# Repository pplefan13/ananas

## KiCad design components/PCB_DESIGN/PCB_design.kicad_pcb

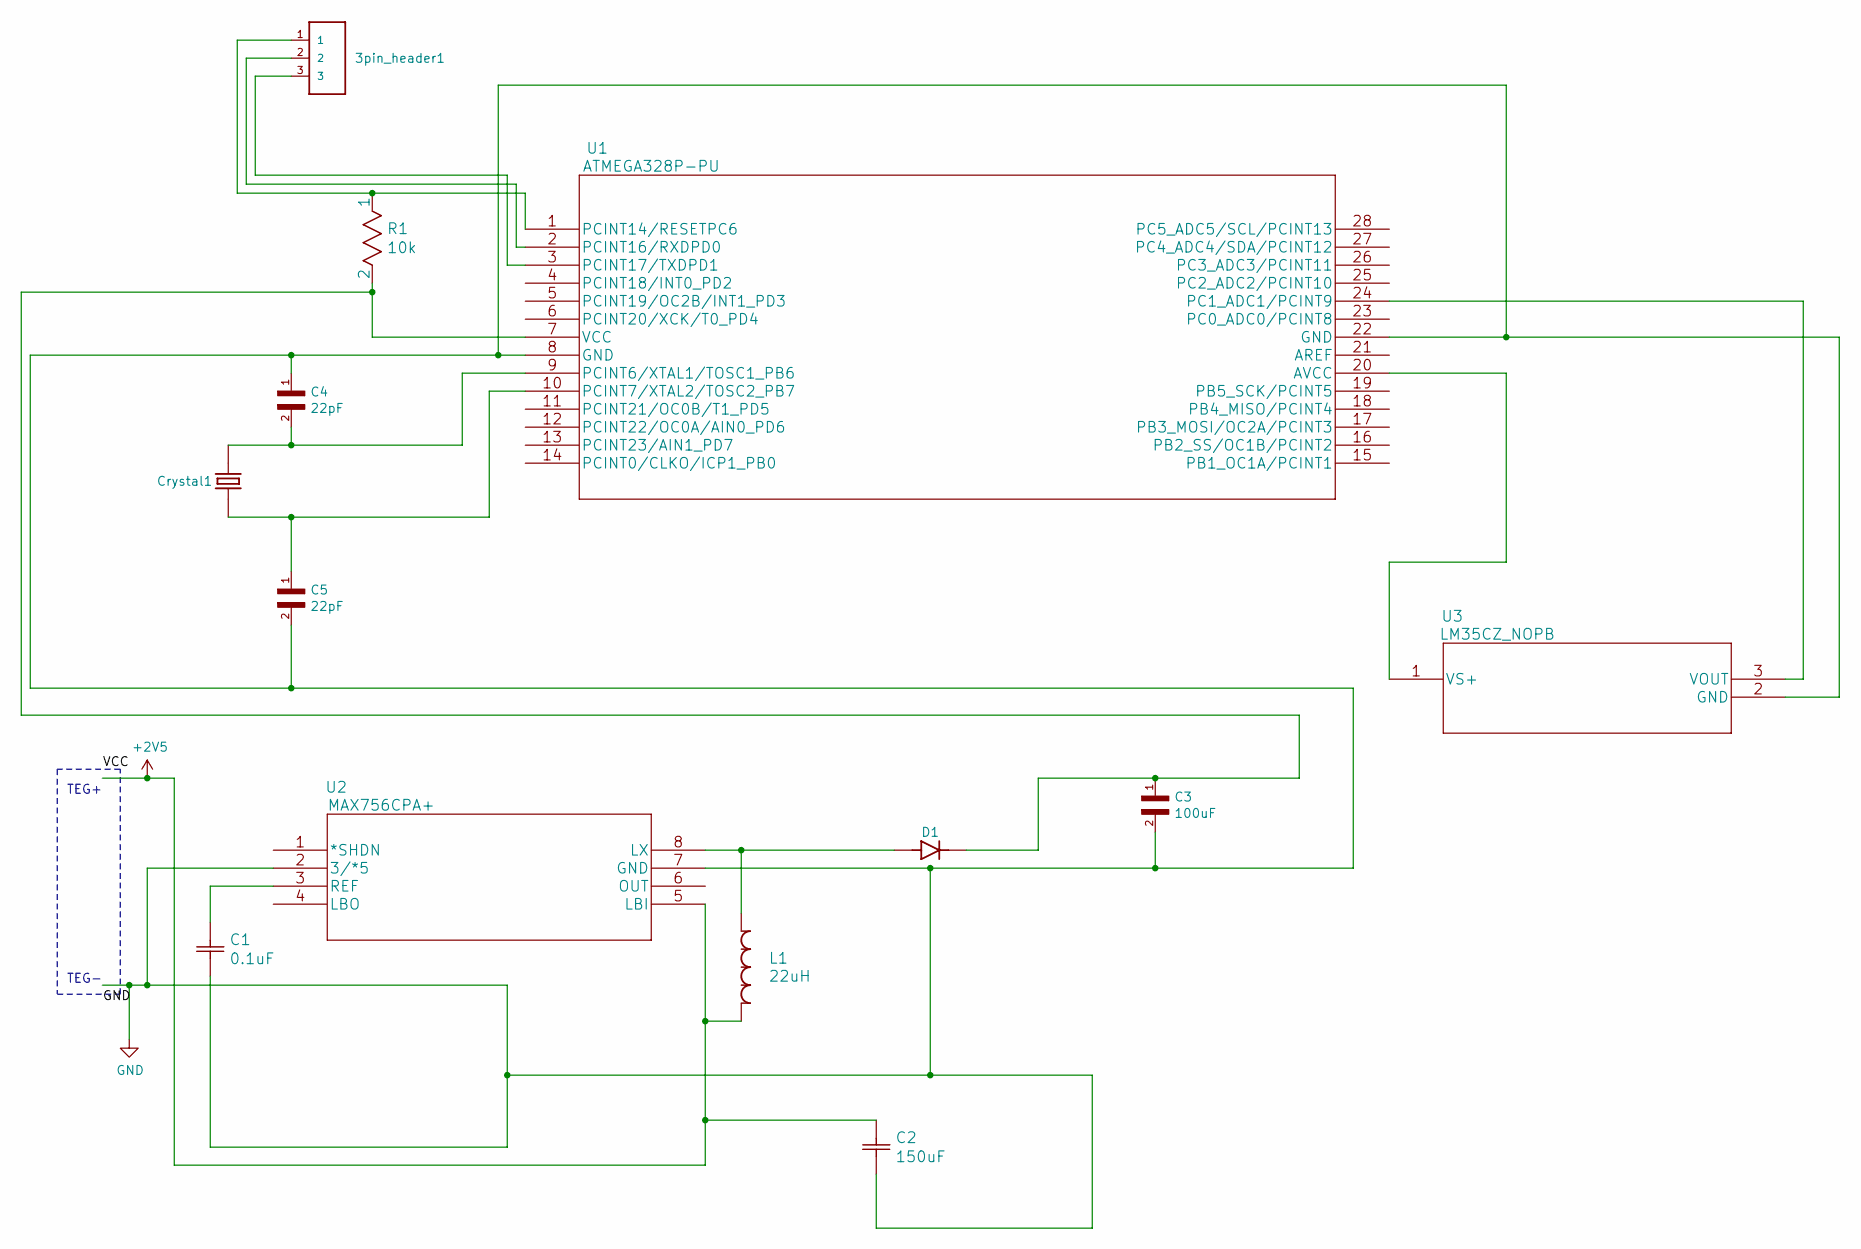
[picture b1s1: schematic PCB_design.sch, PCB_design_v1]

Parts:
3pin_header1: M20-9990345; HDRV3W64P254_1X3_762X254X910P
C1: 0.1uF; UMA1H0R1MCD2TP
C2: 150uF; LGN2W151MELZ40
C3: 100uF; CAPC1005X55N
C4, C5: 22pF; CAPC3216X190N
Crystal1: ECS-110.5-20-5PX-TR; XTAL_ECS-110.5-20-5PX-TR
D1: .; SODFL1608X70N
L1: 22uH; SRR1260-220M
R1: 10k; CF14JT10K0
U1: ATMEGA328P-PU
U2: MAX756CPA+; MAX756CPA&plus_
U3: LM35CZ_NOPB; LM35CZ&slash_NOPB

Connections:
+2V5: C2.1, L1.1, U2.5 (LBI)
GND: C1.2, C2.2, C3.2, C4.1, C5.2, U1.8 (GND), U1.22 (GND), U2.2 (3/*5), U2.7 (GND), U3.2 (GND)
unnamed: 3pin_header1.1, R1.1, U1.1 (PCINT14/RESETPC6)
unnamed: 3pin_header1.2, U1.2 (PCINT16/RXDPD0)
unnamed: 3pin_header1.3, U1.3 (PCINT17/TXDPD1)
unnamed: C1.1, U2.3 (REF)
unnamed: C3.1, D1.C (K), R1.2, U1.7 (VCC)
unnamed: C4.2, Crystal1.1, U1.9 (PCINT6/XTAL1/TOSC1_PB6)
unnamed: C5.1, Crystal1.2, U1.10 (PCINT7/XTAL2/TOSC2_PB7)
unnamed: D1.A, L1.2, U2.8 (LX)
unnamed: U1.20 (AVCC), U3.1 (VS+)
unnamed: U1.24 (PC1_ADC1/PCINT9), U3.3 (VOUT)

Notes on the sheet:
TEG+
TEG-

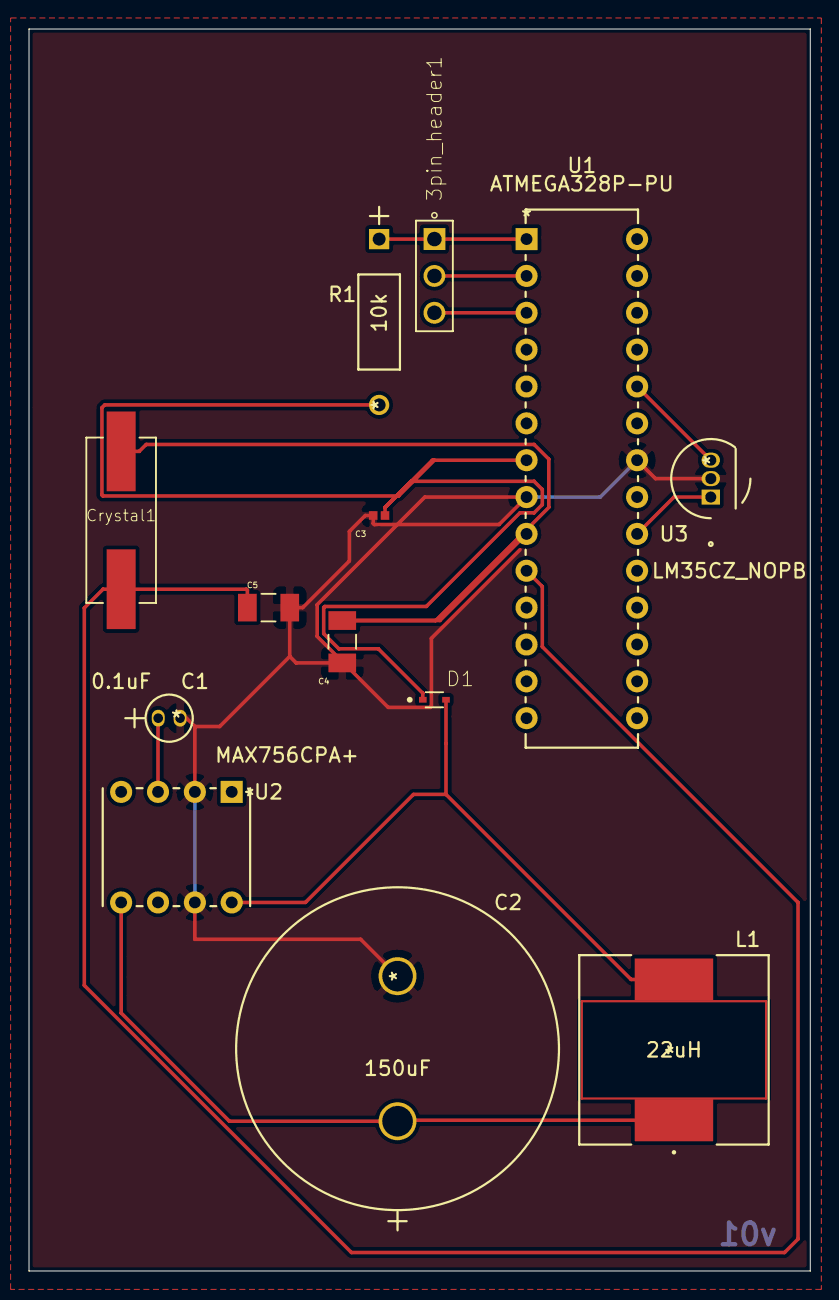
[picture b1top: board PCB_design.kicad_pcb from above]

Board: 2 copper layers, 53.8 x 85.6 mm, 13 parts (0 on the bottom side), 12 nets.

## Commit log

2025-08-04 commit_message
2025-08-04 added mimi
2025-08-04 deleted text files
2025-08-04 added text files
2025-08-04 deleted json files
2025-08-04 display splacing
2025-08-04 dates update
2025-08-24 js folder
2025-08-24 data added
2025-08-24 data freedom
2025-08-24 free
2025-08-30 Update frigider.html functions link
2025-08-30 Update ananasite.html functions link
2025-08-30 vsc update to all
2025-08-30 array array_problem
2025-08-30 modified
2025-08-31 local storage handling
2025-09-01 fixed remove function
2025-09-01 del ?v2 from ico
2025-09-01 ico management
2025-09-01 date jail
2025-09-01 load check
2025-09-01 no more node.js
2025-09-09 file_handling
2025-09-10 wifi credentials
2025-09-10 functions clean
2025-09-10 function cleanup
2025-09-10 exp display
2025-09-12 automation pt 1
2025-09-12 shell script & ini config
